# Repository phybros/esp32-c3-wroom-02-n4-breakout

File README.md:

# Breakout Board for ESP32-C3-WROOM-02

This repo contains all the design files to make a breakout board for the ESP32-C3-WROOM-02-N4 and ESP32-C3-WROOM-02U-N4 which will allow you to use the ESP module on a breadboard.

The project was created using KiCAD v7.

Read more about the project and see more photos here: <https://willwarren.com/2023/12/06/breakout-board-esp32-c3-wroom-02-wifi-module/>

## License

This repo is licensed under the [Attribution-ShareAlike 4.0 license (CC BY-SA 4.0)](https://creativecommons.org/licenses/by-sa/4.0/)

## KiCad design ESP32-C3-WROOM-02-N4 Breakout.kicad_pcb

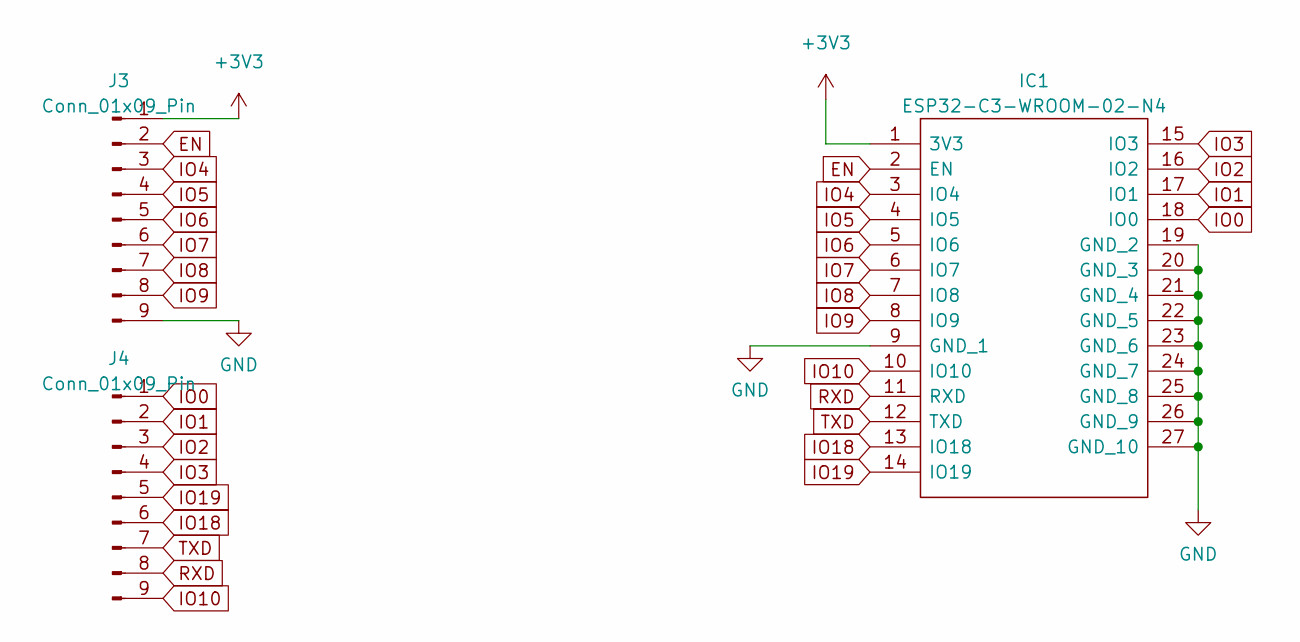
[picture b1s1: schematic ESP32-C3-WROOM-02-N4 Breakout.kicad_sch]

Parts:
IC1: ESP32-C3-WROOM-02-N4; ESP32C3WROOM02N4; Manufacturer_Part_Number ESP32-C3-WROOM-02-N4; Mouser Part Number 356-ESP32C3WROOM02N4
J3, J4: Conn_01x09_Pin; PinHeader_1x09_P2.54mm_Vertical

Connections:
+3V3: IC1.1 (3V3), J3.1
EN: IC1.2 (EN), J3.2
GND: IC1.9 (GND_1), IC1.19 (GND_2), IC1.20 (GND_3), IC1.21 (GND_4), IC1.22 (GND_5), IC1.23 (GND_6), IC1.24 (GND_7), IC1.25 (GND_8), IC1.26 (GND_9), IC1.27 (GND_10), J3.9
IO0: IC1.18 (IO0), J4.1
IO1: IC1.17 (IO1), J4.2
IO2: IC1.16 (IO2), J4.3
IO3: IC1.15 (IO3), J4.4
IO4: IC1.3 (IO4), J3.3
IO5: IC1.4 (IO5), J3.4
IO6: IC1.5 (IO6), J3.5
IO7: IC1.6 (IO7), J3.6
IO8: IC1.7 (IO8), J3.7
IO9: IC1.8 (IO9), J3.8
IO10: IC1.10 (IO10), J4.9
IO18: IC1.13 (IO18), J4.6
IO19: IC1.14 (IO19), J4.5
RXD: IC1.11 (RXD), J4.8
TXD: IC1.12 (TXD), J4.7

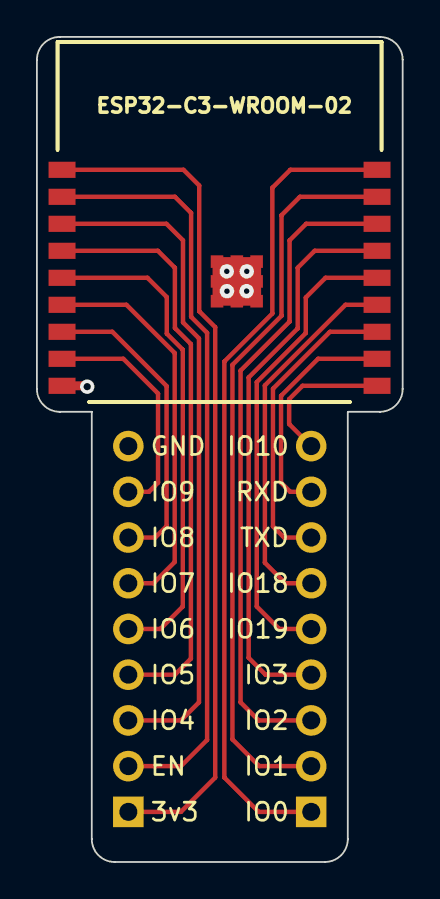
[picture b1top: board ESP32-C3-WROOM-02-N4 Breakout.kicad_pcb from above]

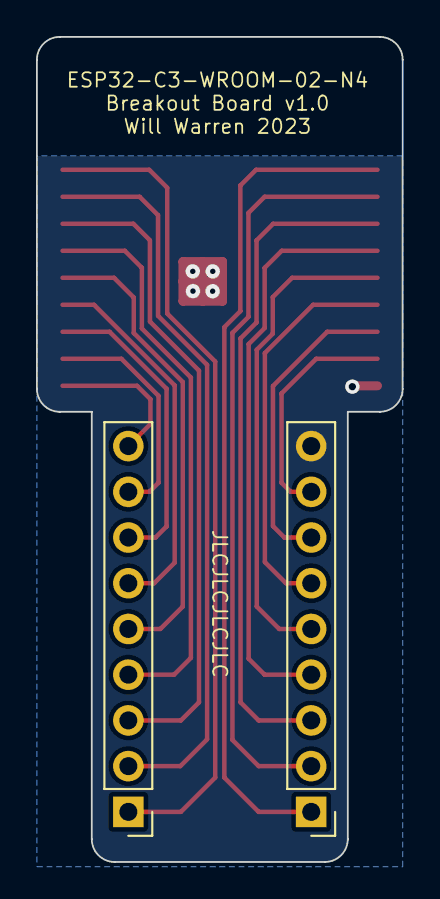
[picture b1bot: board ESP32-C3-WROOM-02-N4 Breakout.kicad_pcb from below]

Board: 2 copper layers, 20.3 x 45.8 mm, 3 parts (2 on the bottom side), 18 nets.

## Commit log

2023-12-06 🥰 initial import
